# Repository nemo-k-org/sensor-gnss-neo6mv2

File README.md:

# Nemo-K location (GNSS) sensor for NEO 6M breakout board GY-NEO6MV2 

## Overview

This is Nemo-K board for ESP-01 and NEO 6M GNSS breakout board typically labelled
as `GY-NEO6MV2`. The board is widely available in stores selling Arduino-IoT related stuff.

The board sends GNSS information to Signal K server.

The board is designed to be used with ESP-01 microcontroller running Nemo-K firmware.

To build you need
 * The PCB
 * ESP-01S
 * NEO 6M GNSS breakout board
 * Four plastic hexagon motherboard spacers (length 8 mm, thread M2.5)
 * Eight M2.5 screws (length max 4 mm)
 * For external GPS antenna: pigtail from [Hirose U.FL](https://en.wikipedia.org/wiki/Hirose_U.FL) to typically
   SMA male/female

## Content

The repository contains schematics and PCB in KiCad 8.0 format. The footprint properties contains LCSC part numbers
used by [JLCPBC.com](https://jlcpcb.com). If present, the `sensor-gnssneo6mv2/production/` contains all necessary
files to order boards from JLCPCB. The production files can be easily re-created using
[KiCad Fabrication Toolkit](https://github.com/bennymeg/Fabrication-Toolkit).

The Nemo-K project is not affiliated or sponsored by JLCPCB. The project does not endorse JLCPCB.

## Changelog

2025-11-15 v3 - Revised after 1st proto
 * Changed power connector footprint to LCSC C5349550
 * Adjusted holes with GPS breakout board
 * Added test pads for voltage

2025-10-26 v2 - First prototype
 * First prototype was sent to production

## Copyright and License

The license and copyright can be found in the file `LICENSE`.

The license and copyright cover only the schematic diagram and the PCB design. It does not cover footprints and other
embedded elements or technical documentation which may or may not be covered by their own licenses.

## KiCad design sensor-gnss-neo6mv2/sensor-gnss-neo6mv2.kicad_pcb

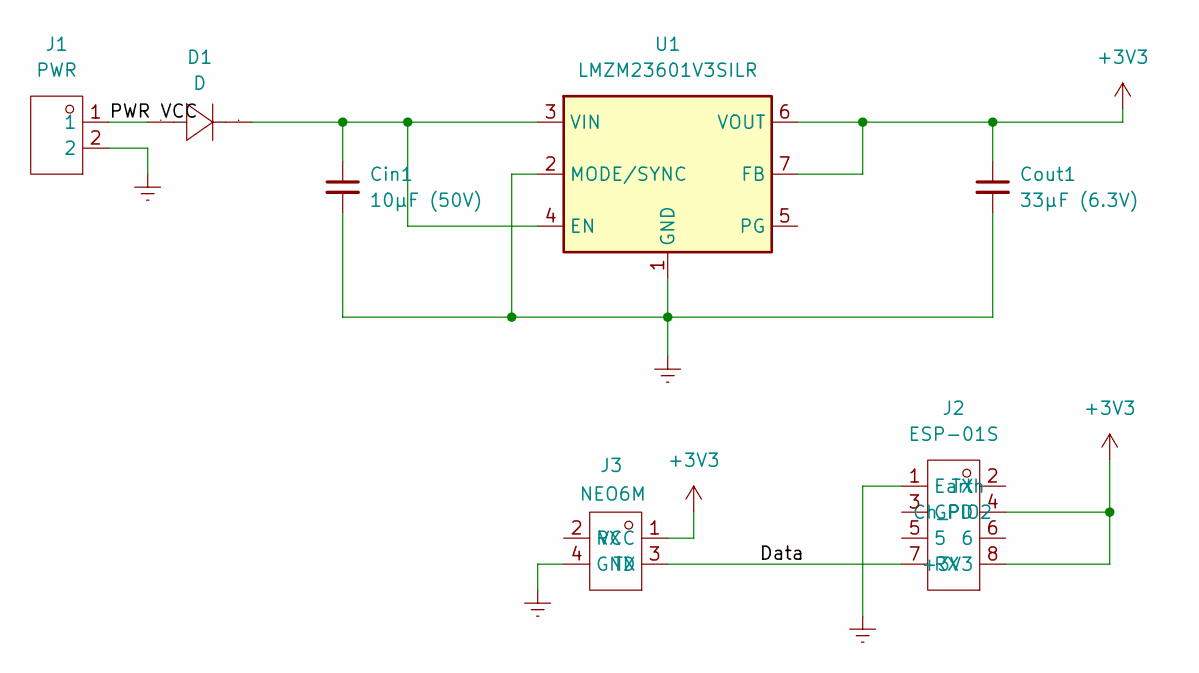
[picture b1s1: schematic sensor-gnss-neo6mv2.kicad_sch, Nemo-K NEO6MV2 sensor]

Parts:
Cin1: 10μF (50V); C_1210_3225Metric; LCSC C2918502
Cout1: 33μF (6.3V); C_1210_3225Metric; Mfg Part C3225X5R1A336MT0A0E; LCSC C531418
D1: D; SOD-323_L1.7-W1.3-LS2.5-RD; Manufacturer Part S7116-300A; LCSC Part Name S7116-300A
J1: PWR; CONN-TH_MX127S-3.81-02P-GN01-CU-Y-A; MPN OSTOQ053251; LCSC C5349550
J2: ESP-01S; HDR-SMD_8P-P2.54-V-F-R2-C4-S7.1; Mfg Part PM254-2-04-S-8.5; LCSC C3975149
J3: NEO6M; HDR-SMD_HX-PM2.54-1X4P-TP-YQ; Manufacturer Part HX PM2.54-1x4P TP-YQ; LCSC Part Name 间距:2.54mm 1x4P 立贴 (交错脚)
U1: LMZM23601V3SILR; Texas_SIL0010A_MicroSiP-10-1EP_3.8x3mm_P0.6mm_EP0.7x2.9mm_T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; MPN LMZM23601SILR; LCSC C2864948

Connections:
+3V3: Cout1.1, J2.4 (Ch_PD), J2.8 (+3V3), J3.1 (VCC), U1.6 (VOUT), U1.7 (FB)
/Data: J2.7 (RX), J3.3 (TX)
/PWR VCC: D1.2 (A), J1.1
Earth: Cin1.2, Cout1.2, J1.2, J2.1 (Earth), J3.4 (GND), U1.1 (GND), U1.2 (MODE/SYNC), U1.11 (GND)
unnamed: Cin1.1, D1.1 (K), U1.3 (VIN), U1.4 (EN)

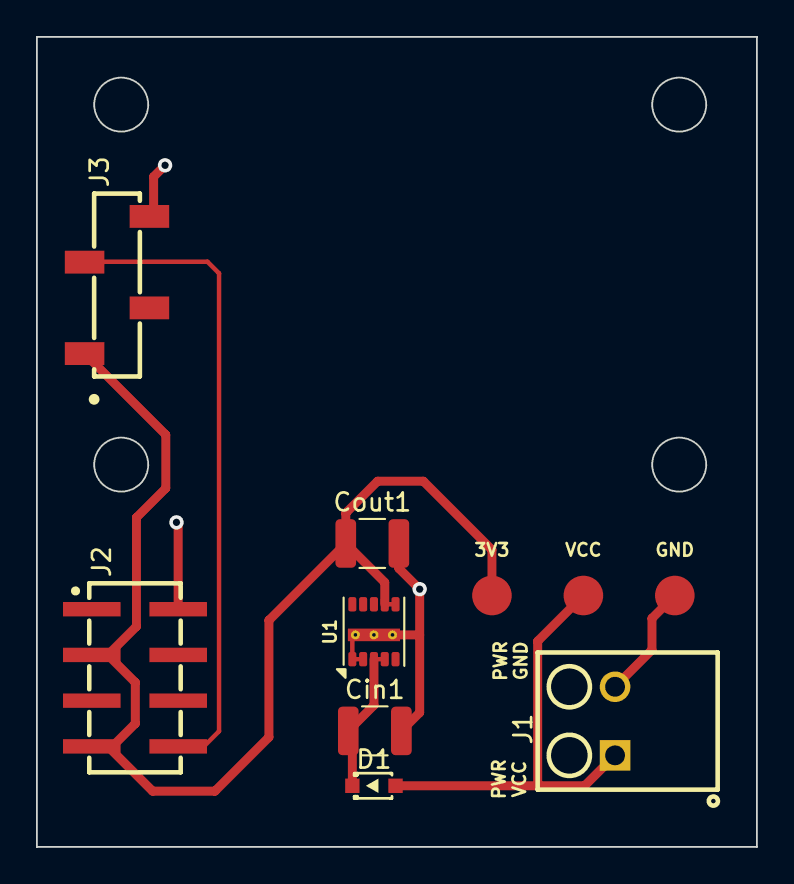
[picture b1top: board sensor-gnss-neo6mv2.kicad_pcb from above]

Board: 2 copper layers, 40.0 x 45.0 mm, 7 parts (0 on the bottom side), 5 nets.

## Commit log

2025-10-08 Initial version
2025-10-09 Added NEO 6M datasheet
2025-10-09 First sketch of the schematics & PCB
2025-10-26 First prototype sent to production
2025-11-15 v3, revised based on first proto version
